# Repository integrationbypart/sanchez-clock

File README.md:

# sanchez-clock
 My first HPS Clock
 (gerbers are in rectangle-clock, or zip file already here in this directory)

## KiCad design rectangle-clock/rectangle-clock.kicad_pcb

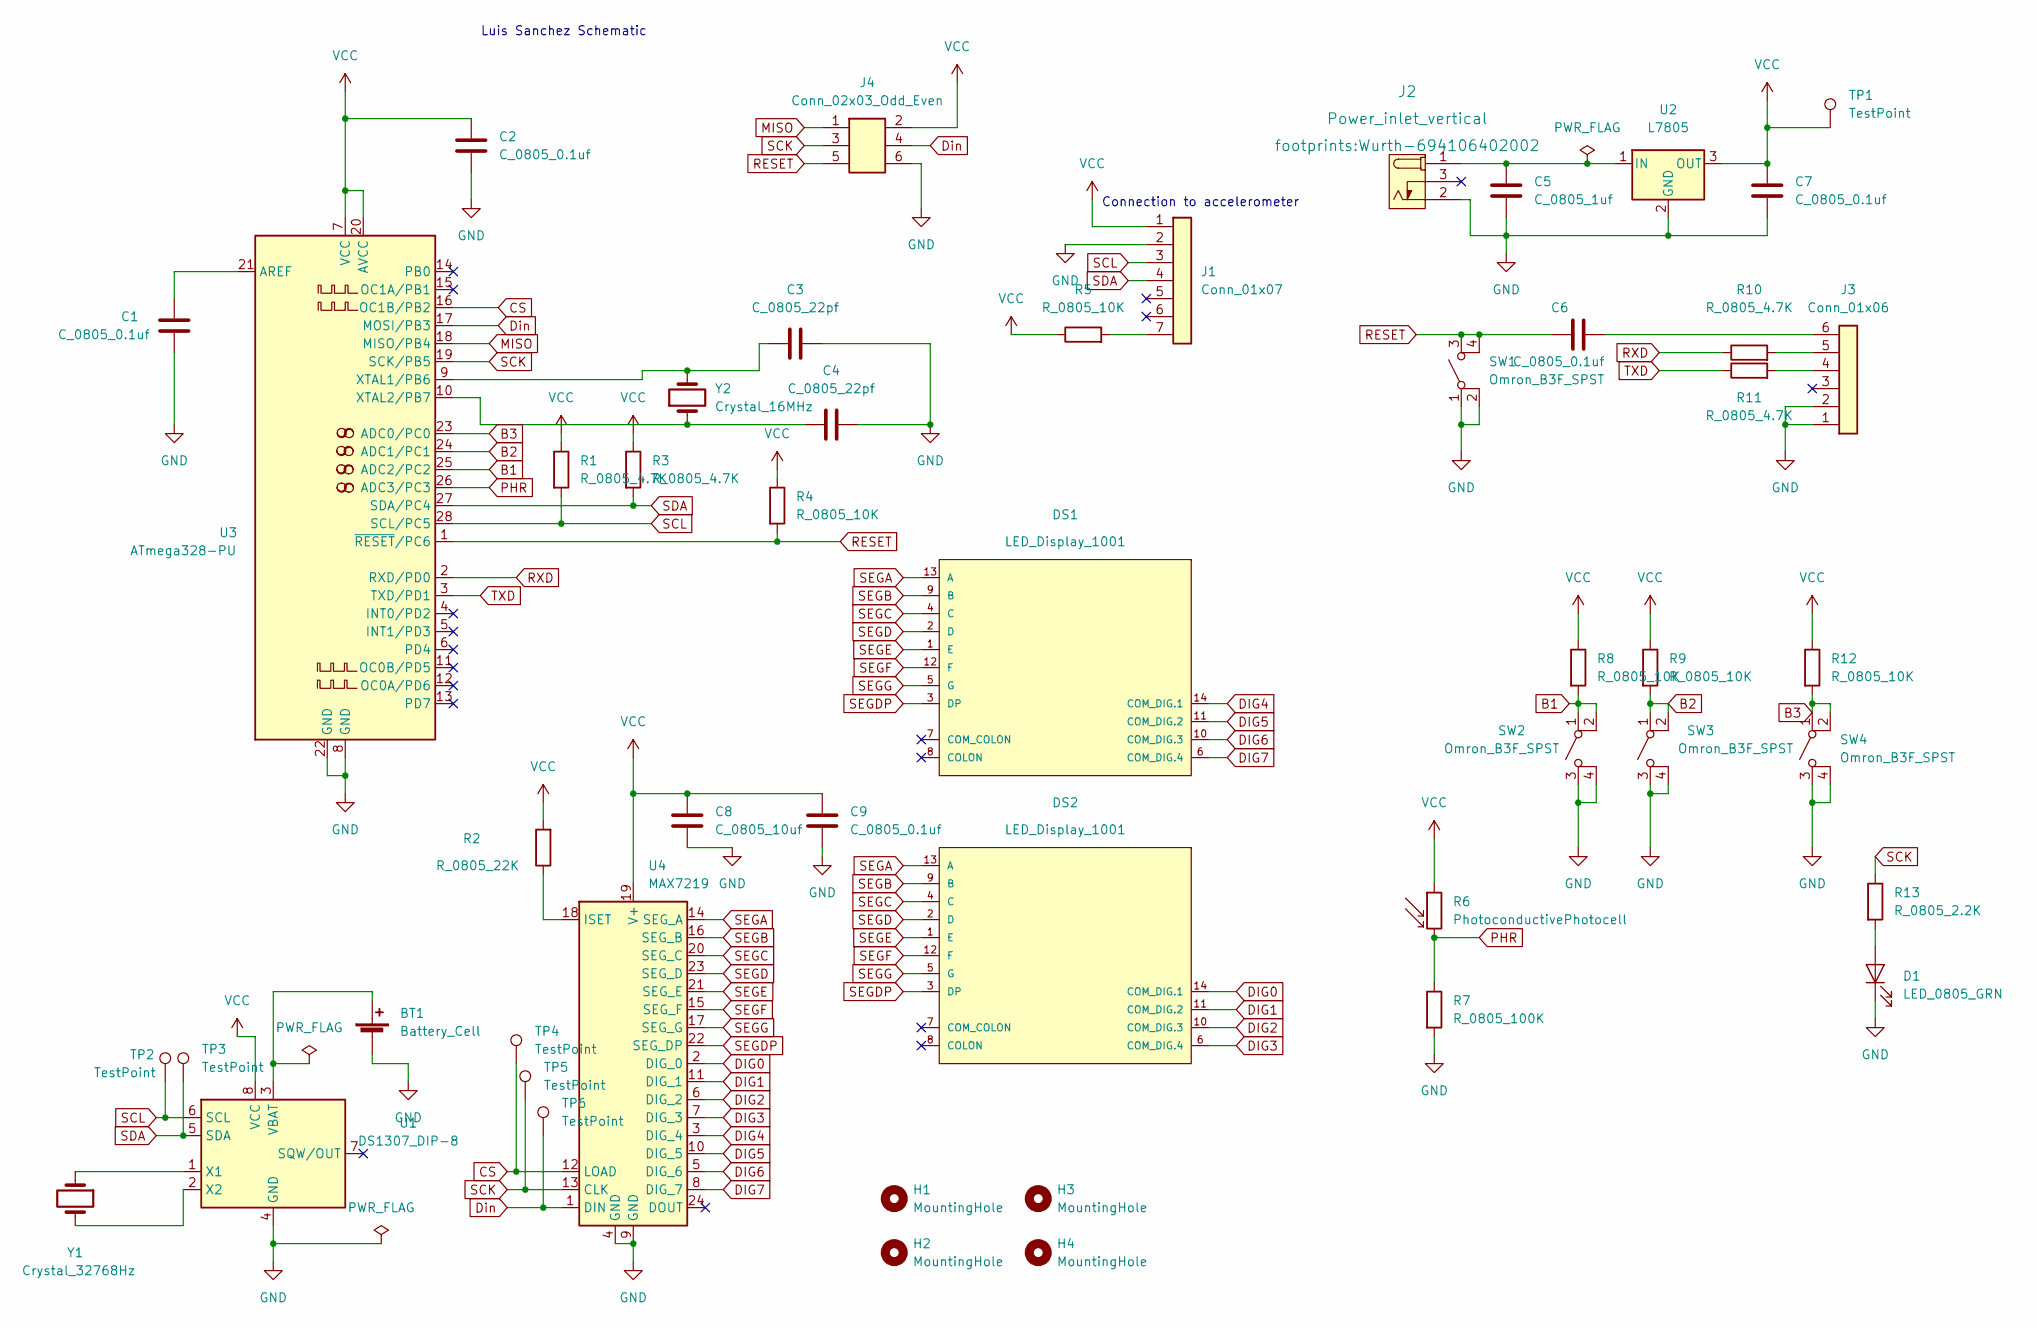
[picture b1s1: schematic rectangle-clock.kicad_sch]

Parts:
BT1: Battery_Cell; BatteryHolder_Keystone_106_1x20mm; MPN BS-7; Digikey PN BS-7-ND
C1, C2, C6, C7, C9: C_0805_0.1uf; C_0805_2012Metric; Voltage N/A; Tolerance N/A; MPN 08055C104KAT2A; Digikey PN 478-1395-1-ND
C3, C4: C_0805_22pf; C_0805_2012Metric; Voltage N/A; Tolerance N/A; MPN CC0805JRNPO9BN220; Digikey PN 311-1103-1-ND
C5: C_0805_1uf; C_0805_2012Metric; Voltage N/A; Tolerance N/A; MPN CC0805KKX7R8BB105; Digikey PN 311-1456-1-ND
C8: C_0805_10uf; C_0805_2012Metric; Voltage N/A; Tolerance N/A; MPN GRM21BR61E106KA73L; Digikey PN 490-5523-1-ND
D1: LED_0805_GRN; LED_0805_2012Metric; MPN 150080VS75000; Digikey PN 732-4986-1-ND
DS1, DS2: LED_Display_1001; Adafruit-1001-0-0-MFG; forward voltage 3.2V; reverse voltage 5V; mouser part number 485-1001; digikey description WHITE 7-SEGMENT CLOCK DISPLAY
H1, H2, H3, H4: MountingHole; MountingHole_3.2mm_M3
J1: Conn_01x07; PinHeader_1x07_P2.54mm_Vertical; MPN 61300711121; Digikey PN 732-5320-ND
J2: Power_inlet_vertical; Wurth-694106402002; MPN 694106402002; Digikey PN 732-5931-ND
J3: Conn_01x06; PinHeader_1x06_P2.54mm_Vertical; MPN 61300611121; Digikey PN 732-5319-ND
J4: Conn_02x03_Odd_Even; PinHeader_2x03_P2.54mm_Vertical; MPN PRPC003DAAN-RC; Digikey PN S2011EC-03-ND
R1, R3, R10, R11: R_0805_4.7K; R_0805_2012Metric; Tolerance N/A; MPN RC0805FR-074K7L; Digikey PN 311-4.70KCRCT-ND
R2: R_0805_22K; R_0805_2012Metric; Tolerance N/A; MPN RC0805FR-0722KL; Digikey PN 311-22.0KCRCT-ND
R4, R5, R8, R9, R12: R_0805_10K; R_0805_2012Metric; Tolerance N/A; MPN RC0805FR-0710KL; Digikey PN 311-10.0KCRCT-ND
R6: PhotoconductivePhotocell; R_LDR_4.9x4.2mm_P2.54mm_Vertical; Voltage N/A; Tolerance N/A; MPN PDV-P8103; Digikey PN PDV-P8103-ND
R7: R_0805_100K; R_0805_2012Metric; Tolerance N/A; MPN RC0805FR-07100KL; Digikey PN 311-100KCRCT-ND
R13: R_0805_2.2K; R_0805_2012Metric; Tolerance N/A; MPN N/A; Digikey PN 311-2.20KCRCT-ND
SW1, SW2, SW3, SW4: Omron_B3F_SPST; SW_SPST_Omron_B3FS-100xP; MPN B3FS-1000P; Digikey PN SW423CT-ND
TP1, TP2, TP3, TP4, TP5, TP6: TestPoint; TestPoint_THTPad_D2.0mm_Drill1.0mm
U1: DS1307_DIP-8; DIP-8_W7.62mm; MPN A 08-LC-TT; Digikey PN AE9986-ND
U2: L7805; TO-252-2; MPN L7805CDT-TR; Digikey PN 497-7255-1-ND
U3: ATmega328-PU; DIP-28_W7.62mm; MPN ED281DT; Digikey PN ED3050-5-ND
U4: MAX7219; DIP-24_W7.62mm; MPN ED241DT; Digikey PN ED3049-5-ND
Y1: Crystal_32768Hz; Crystal_SMD_2Pin_3.2x1.5mm; MPN Q 0,032768-JTX310-12,5-20-T1-HMR-50K-LF; Digikey PN 1908-1314-1-ND
Y2: Crystal_16MHz; Crystal_SMD_HC49-SD; MPN ECS-160-20-5PXDN-TR; Digikey PN XC1299CT-ND

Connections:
B1: R8.2, SW2.1 (A), SW2.2 (A), U3.25 (ADC2/PC2)
B2: R9.2, SW3.1 (A), SW3.2 (A), U3.24 (ADC1/PC1)
B3: R12.2, SW4.1 (A), SW4.2 (A), U3.23 (ADC0/PC0)
CS: TP4.1, U3.16 (OC1B/PB2), U4.12 (LOAD)
DIG0: DS2.14 (COM_DIG.1), U4.2 (DIG_0)
DIG1: DS2.11 (COM_DIG.2), U4.11 (DIG_1)
DIG2: DS2.10 (COM_DIG.3), U4.6 (DIG_2)
DIG3: DS2.6 (COM_DIG.4), U4.7 (DIG_3)
DIG4: DS1.14 (COM_DIG.1), U4.3 (DIG_4)
DIG5: DS1.11 (COM_DIG.2), U4.10 (DIG_5)
DIG6: DS1.10 (COM_DIG.3), U4.5 (DIG_6)
DIG7: DS1.6 (COM_DIG.4), U4.8 (DIG_7)
Din: J4.4, TP6.1, U3.17 (MOSI/PB3), U4.1 (DIN)
GND: BT1.2 (-), C1.2, C2.2, C3.2, C4.2, C5.2, C7.2, C8.2, C9.2, D1.1 (K), J1.2, J2.2 (OUT), J3.1, J3.2, J4.6, R7.2, SW1.1 (A), SW1.2 (A), SW2.3 (B), SW2.4 (B), SW3.3 (B), SW3.4 (B), SW4.3 (B), SW4.4 (B), U1.4 (GND), U2.2 (GND), U3.8 (GND), U3.22 (GND), U4.4 (GND), U4.9 (GND)
MISO: J4.1, U3.18 (MISO/PB4)
unnamed: BT1.1 (+), U1.3 (VBAT)
unnamed: C1.1, U3.21 (AREF)
unnamed: C3.1, U3.9 (XTAL1/PB6), Y2.2
unnamed: C4.1, U3.10 (XTAL2/PB7), Y2.1
unnamed: C5.1, J2.1 (POLE), U2.1 (IN)
unnamed: C6.2, J3.6
unnamed: D1.2 (A), R13.2
unnamed: J1.7, R5.2
unnamed: J3.4, R11.2
unnamed: J3.5, R10.2
unnamed: R2.1, U4.18 (ISET)
unnamed: U1.1 (X1), Y1.1
unnamed: U1.2 (X2), Y1.2
PHR: R6.2, R7.1, U3.26 (ADC3/PC3)
RESET: C6.1, J4.5, R4.2, SW1.3 (B), SW1.4 (B), U3.1 (~RESET/PC6)
RXD: R10.1, U3.2 (RXD/PD0)
SCK: J4.3, R13.1, TP5.1, U3.19 (SCK/PB5), U4.13 (CLK)
SCL: J1.3, R1.2, TP2.1, U1.6 (SCL), U3.28 (SCL/PC5)
SDA: J1.4, R3.2, TP3.1, U1.5 (SDA), U3.27 (SDA/PC4)
SEGA: DS1.13 (A), DS2.13 (A), U4.14 (SEG_A)
SEGB: DS1.9 (B), DS2.9 (B), U4.16 (SEG_B)
SEGC: DS1.4 (C), DS2.4 (C), U4.20 (SEG_C)
SEGD: DS1.2 (D), DS2.2 (D), U4.23 (SEG_D)
SEGDP: DS1.3 (DP), DS2.3 (DP), U4.22 (SEG_DP)
SEGE: DS1.1 (E), DS2.1 (E), U4.21 (SEG_E)
SEGF: DS1.12 (F), DS2.12 (F), U4.15 (SEG_F)
SEGG: DS1.5 (G), DS2.5 (G), U4.17 (SEG_G)
TXD: R11.1, U3.3 (TXD/PD1)
VCC: C2.1, C7.1, C8.1, C9.1, J1.1, J4.2, R1.1, R2.2, R3.1, R4.1, R5.1, R6.1, R8.1, R9.1, R12.1, TP1.1, U1.8 (VCC), U2.3 (OUT), U3.7 (VCC), U3.20 (AVCC), U4.19 (V+)

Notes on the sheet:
Connection to accelerometer
Luis Sanchez Schematic

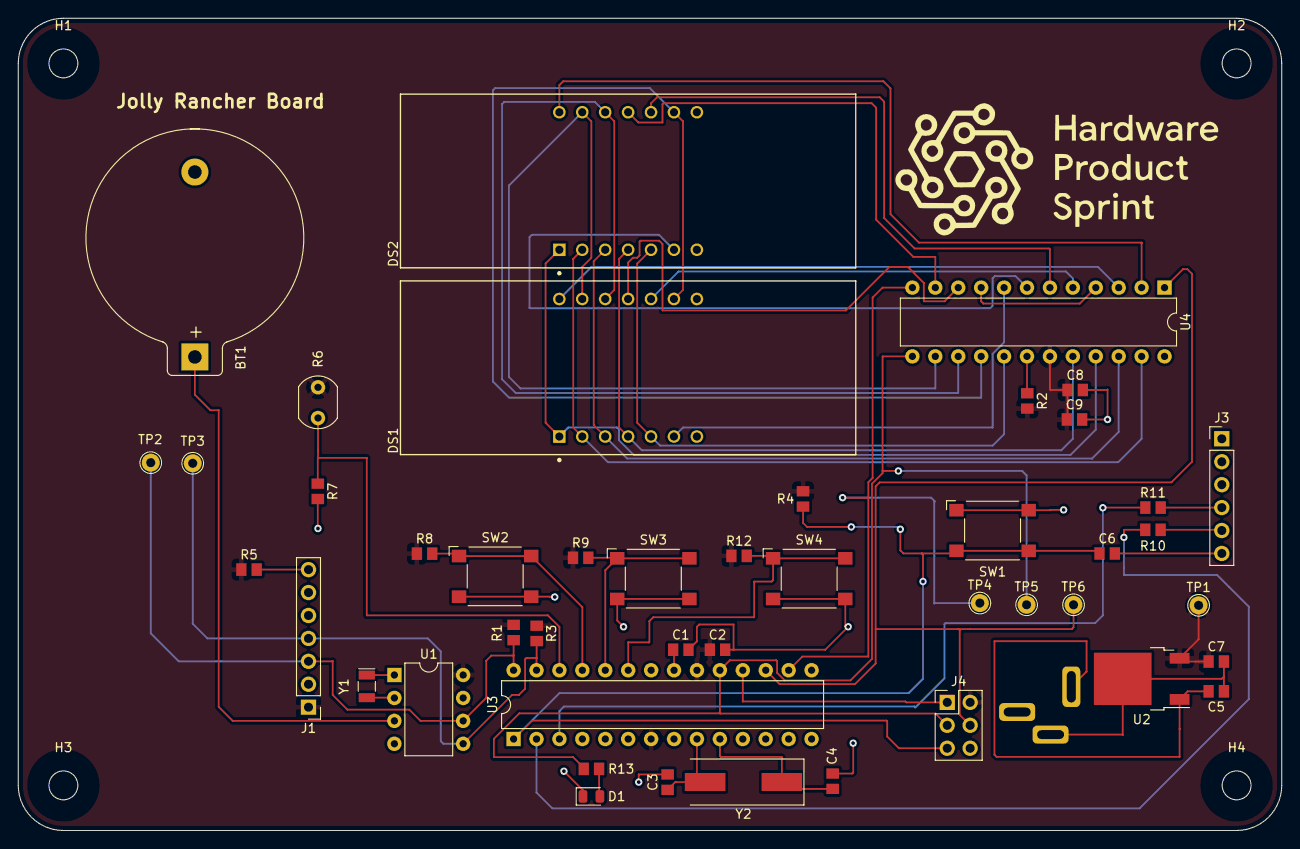
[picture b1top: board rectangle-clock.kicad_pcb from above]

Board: 2 copper layers, 140.0 x 90.0 mm, 50 parts (1 on the bottom side), 44 nets.

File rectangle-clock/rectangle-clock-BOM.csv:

"Id";"Designator";"Package";"Quantity";"Designation";"Supplier and ref";
1;"H4,H2,H3,H1";"MountingHole_3.2mm_M3";4;"MountingHole";;;
2;"DS1,DS2";"Adafruit-1001-0-0-MFG";2;"LED_Display_1001";;;
3;"SW3,SW4,SW2,SW1";"SW_SPST_Omron_B3FS-100xP";4;"Omron_B3F_SPST";;;
4;"C4,C3";"C_0805_2012Metric";2;"C_0805_22pf";;;
5;"TP6,TP3,TP4,TP5,TP1,TP2";"TestPoint_THTPad_D2.0mm_Drill1.0mm";6;"TestPoint";;;
6;"C2,C7,C6,C1";"C_0805_2012Metric";4;"C_0805_0.1uf";;;
7;"J1";"PinHeader_1x07_P2.54mm_Vertical";1;"Conn_01x07";;;
8;"Y1";"Crystal_SMD_2Pin_3.2x1.5mm";1;"Crystal_32768Hz";;;
9;"J2";"Wurth-694106402002";1;"Power_inlet_vertical";;;
10;"BT1";"BatteryHolder_Keystone_106_1x20mm";1;"Battery_Cell";;;
11;"U4";"DIP-24_W7.62mm";1;"MAX7219";;;
12;"R2,R4,R5,R3,R1";"R_0805_2012Metric";5;"R_0805_10K";;;
13;"R6";"R_LDR_4.9x4.2mm_P2.54mm_Vertical";1;"PhotoconductivePhotocell";;;
14;"C5";"C_0805_2012Metric";1;"C_0805_1uf";;;
15;"R9,R8,R12,R7";"R_0805_2012Metric";4;"R_0805_1K";;;
16;"R13";"R_0805_2012Metric";1;"R_0805_2.2K";;;
17;"U1";"DIP-8_W7.62mm";1;"DS1307_DIP-8";;;
18;"Y2";"Crystal_SMD_HC49-SD";1;"Crystal_16MHz";;;
19;"R11,R10";"R_0805_2012Metric";2;"R_0805_4.7K";;;
20;"U2";"TO-252-2";1;"L7805";;;
21;"U3";"DIP-28_W7.62mm";1;"ATmega328-PU";;;
22;"D1";"LED_0805_2012Metric";1;"LED_0805_GRN";;;
23;"J3";"PinHeader_1x06_P2.54mm_Vertical";1;"Conn_01x06";;;

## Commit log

2022-06-01 My first design commit
2022-06-12 Schematic
2022-06-19 updated schematic with battery connections and reset button
2022-06-27 week 3 updates
2022-07-02 Moved schematic to rectangle template
2022-07-19 initial gerber out
2022-07-21 Added Test points
2022-07-21 Final gerber commit
2022-07-21 Board png, .step file
2022-07-21 Final update
2022-07-22 Revised Board/Final Gerber out
2022-07-22 Jolly rancher board image
2022-07-22 Final push? :)
